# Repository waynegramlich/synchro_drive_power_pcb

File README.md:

# synchro_drive_power_pcb

This boad can provide power distribution for up to 4
Synchro Drive Motor PCB's.

## Revision A

Connectors N9, N10, N11, and N12 are 26 pin ribbon cable connectors
that provide:

* Motor power

* Logic power

* CAN bus daisy chain

* 2 Selection lines (Front/Back, Left/Right)

Connector N1 is used to provide 7.2V (i.e. RC battery pack
voltage) for logic power.  Connector N2 is conneceted to a DPDT
switch to turn logic power on and off.

Connectors N3 through N7 provicde a chain of connectors for:

* 2 12 Volt batters for a total of 24 Volts

* A DPDT connection to turn motor power on and off

* 2 emergency stop connection that will disable motor power only.

Connectors N8 and N13 are MakerBus connectors that can be
connected to other MakerBus modules.

Jumper J1 can be used to terminate the CAN bus at N13.

There are 6 test points:

* 2 for logic power/ground.

* 2 for motor power/ground.

* 2 for an extra termination resistor.

There are 4 5mm mounting holes that are on an 80mm by 80mm square.

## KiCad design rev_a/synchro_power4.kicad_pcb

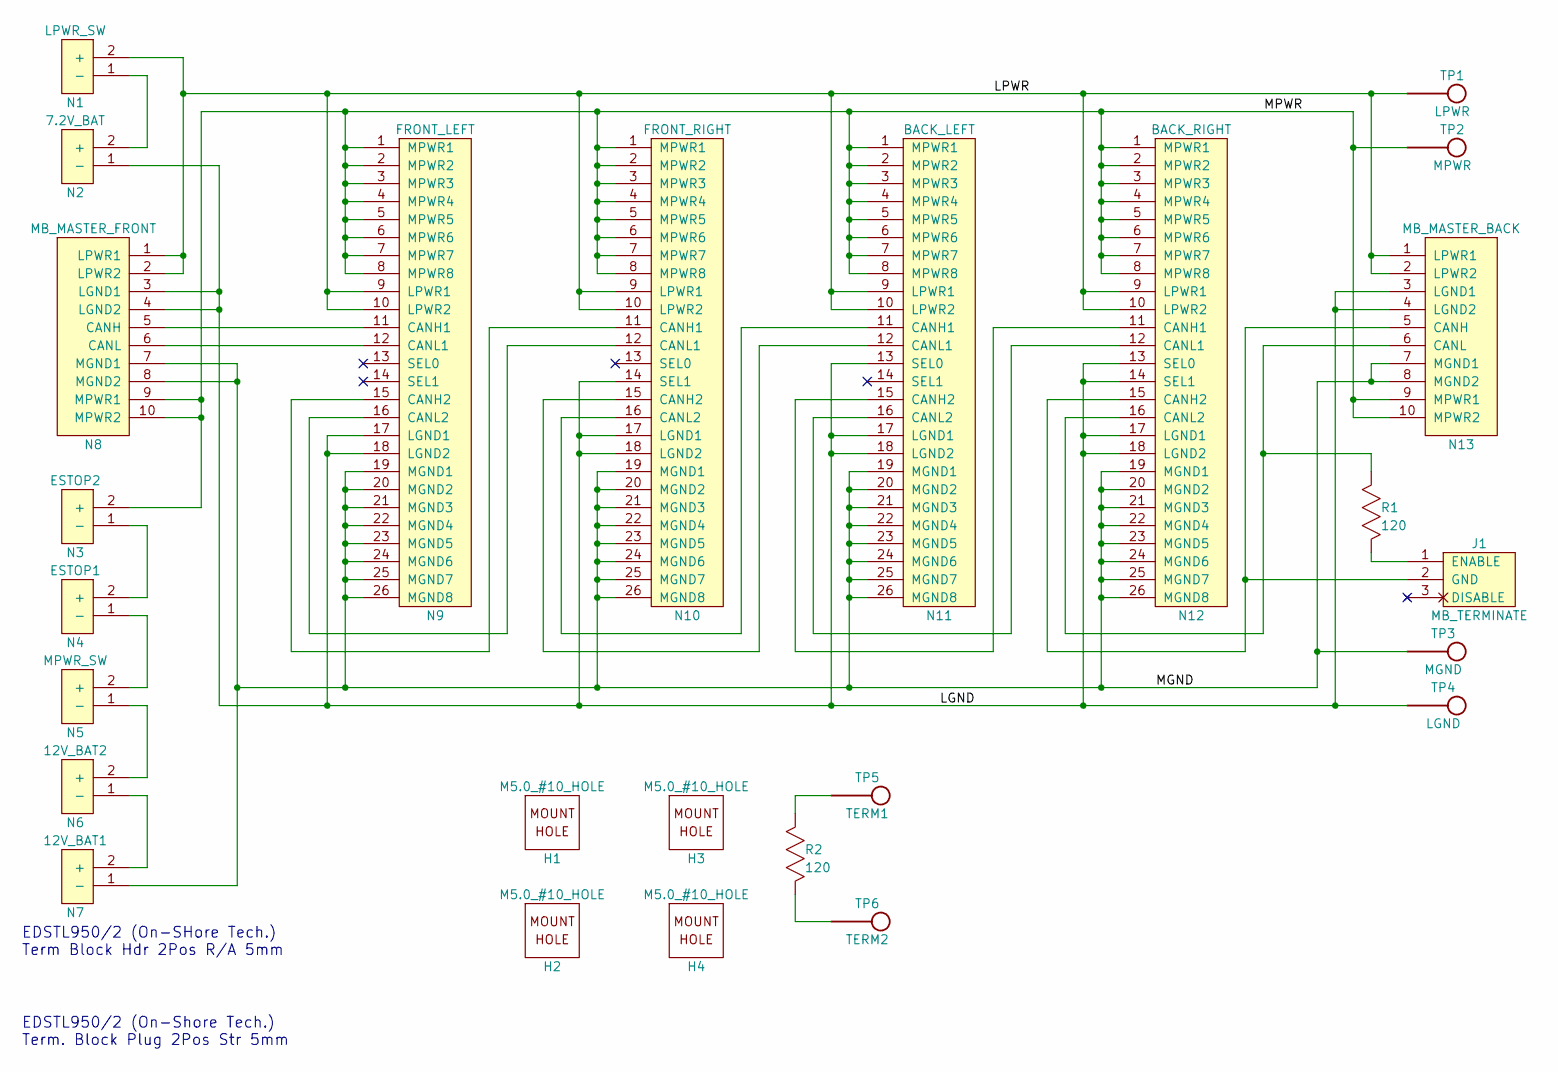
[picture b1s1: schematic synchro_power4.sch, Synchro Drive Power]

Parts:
H1, H2, H3, H4: M5.0_#10_HOLE
J1: MB_TERMINATE
N1: LPWR_SW
N2: 7.2V_BAT
N3: ESTOP2
N4: ESTOP1
N5: MPWR_SW
N6: 12V_BAT2
N7: 12V_BAT1
N8: MB_MASTER_FRONT
N9: FRONT_LEFT
N10: FRONT_RIGHT
N11: BACK_LEFT
N12: BACK_RIGHT
N13: MB_MASTER_BACK
R1, R2: 120
TP1: LPWR
TP2: MPWR
TP3: MGND
TP4: LGND
TP5: TERM1
TP6: TERM2

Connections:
/LGND: N2.1 (-), N8.3 (LGND1), N8.4 (LGND2), N9.17 (LGND1), N9.18 (LGND2), N10.14 (SEL1), N10.17 (LGND1), N10.18 (LGND2), N11.13 (SEL0), N11.17 (LGND1), N11.18 (LGND2), N12.13 (SEL0), N12.14 (SEL1), N12.17 (LGND1), N12.18 (LGND2), N13.3 (LGND1), N13.4 (LGND2), TP4.1
/LPWR: N1.2 (+), N8.1 (LPWR1), N8.2 (LPWR2), N9.9 (LPWR1), N9.10 (LPWR2), N10.9 (LPWR1), N10.10 (LPWR2), N11.9 (LPWR1), N11.10 (LPWR2), N12.9 (LPWR1), N12.10 (LPWR2), N13.1 (LPWR1), N13.2 (LPWR2), TP1.1
/MGND: N7.1 (-), N8.7 (MGND1), N8.8 (MGND2), N9.19 (MGND1), N9.20 (MGND2), N9.21 (MGND3), N9.22 (MGND4), N9.23 (MGND5), N9.24 (MGND6), N9.25 (MGND7), N9.26 (MGND8), N10.19 (MGND1), N10.20 (MGND2), N10.21 (MGND3), N10.22 (MGND4), N10.23 (MGND5), N10.24 (MGND6), N10.25 (MGND7), N10.26 (MGND8), N11.19 (MGND1), N11.20 (MGND2), N11.21 (MGND3), N11.22 (MGND4), N11.23 (MGND5), N11.24 (MGND6), N11.25 (MGND7), N11.26 (MGND8), N12.19 (MGND1), N12.20 (MGND2), N12.21 (MGND3), N12.22 (MGND4), N12.23 (MGND5), N12.24 (MGND6), N12.25 (MGND7), N12.26 (MGND8), N13.7 (MGND1), N13.8 (MGND2), TP3.1
/MPWR: N3.2 (+), N8.9 (MPWR1), N8.10 (MPWR2), N9.1 (MPWR1), N9.2 (MPWR2), N9.3 (MPWR3), N9.4 (MPWR4), N9.5 (MPWR5), N9.6 (MPWR6), N9.7 (MPWR7), N9.8 (MPWR8), N10.1 (MPWR1), N10.2 (MPWR2), N10.3 (MPWR3), N10.4 (MPWR4), N10.5 (MPWR5), N10.6 (MPWR6), N10.7 (MPWR7), N10.8 (MPWR8), N11.1 (MPWR1), N11.2 (MPWR2), N11.3 (MPWR3), N11.4 (MPWR4), N11.5 (MPWR5), N11.6 (MPWR6), N11.7 (MPWR7), N11.8 (MPWR8), N12.1 (MPWR1), N12.2 (MPWR2), N12.3 (MPWR3), N12.4 (MPWR4), N12.5 (MPWR5), N12.6 (MPWR6), N12.7 (MPWR7), N12.8 (MPWR8), N13.9 (MPWR1), N13.10 (MPWR2), TP2.1
unnamed: J1.1 (ENABLE), R1.1
unnamed: J1.2 (GND), N12.15 (CANH2), N13.5 (CANH)
unnamed: N1.1 (-), N2.2 (+)
unnamed: N3.1 (-), N4.2 (+)
unnamed: N4.1 (-), N5.2 (+)
unnamed: N5.1 (-), N6.2 (+)
unnamed: N6.1 (-), N7.2 (+)
unnamed: N8.5 (CANH), N9.11 (CANH1)
unnamed: N8.6 (CANL), N9.12 (CANL1)
unnamed: N9.15 (CANH2), N10.11 (CANH1)
unnamed: N9.16 (CANL2), N10.12 (CANL1)
unnamed: N10.15 (CANH2), N11.12 (CANL1)
unnamed: N10.16 (CANL2), N11.11 (CANH1)
unnamed: N11.15 (CANH2), N12.11 (CANH1)
unnamed: N11.16 (CANL2), N12.12 (CANL1)
unnamed: N12.16 (CANL2), N13.6 (CANL), R1.2
unnamed: R2.1, TP6.1
unnamed: R2.2, TP5.1

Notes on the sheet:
EDSTL950/2 (On-SHore Tech.) Term Block Hdr 2Pos R/A 5mm
EDSTL950/2 (On-Shore Tech.) Term. Block Plug 2Pos Str 5mm

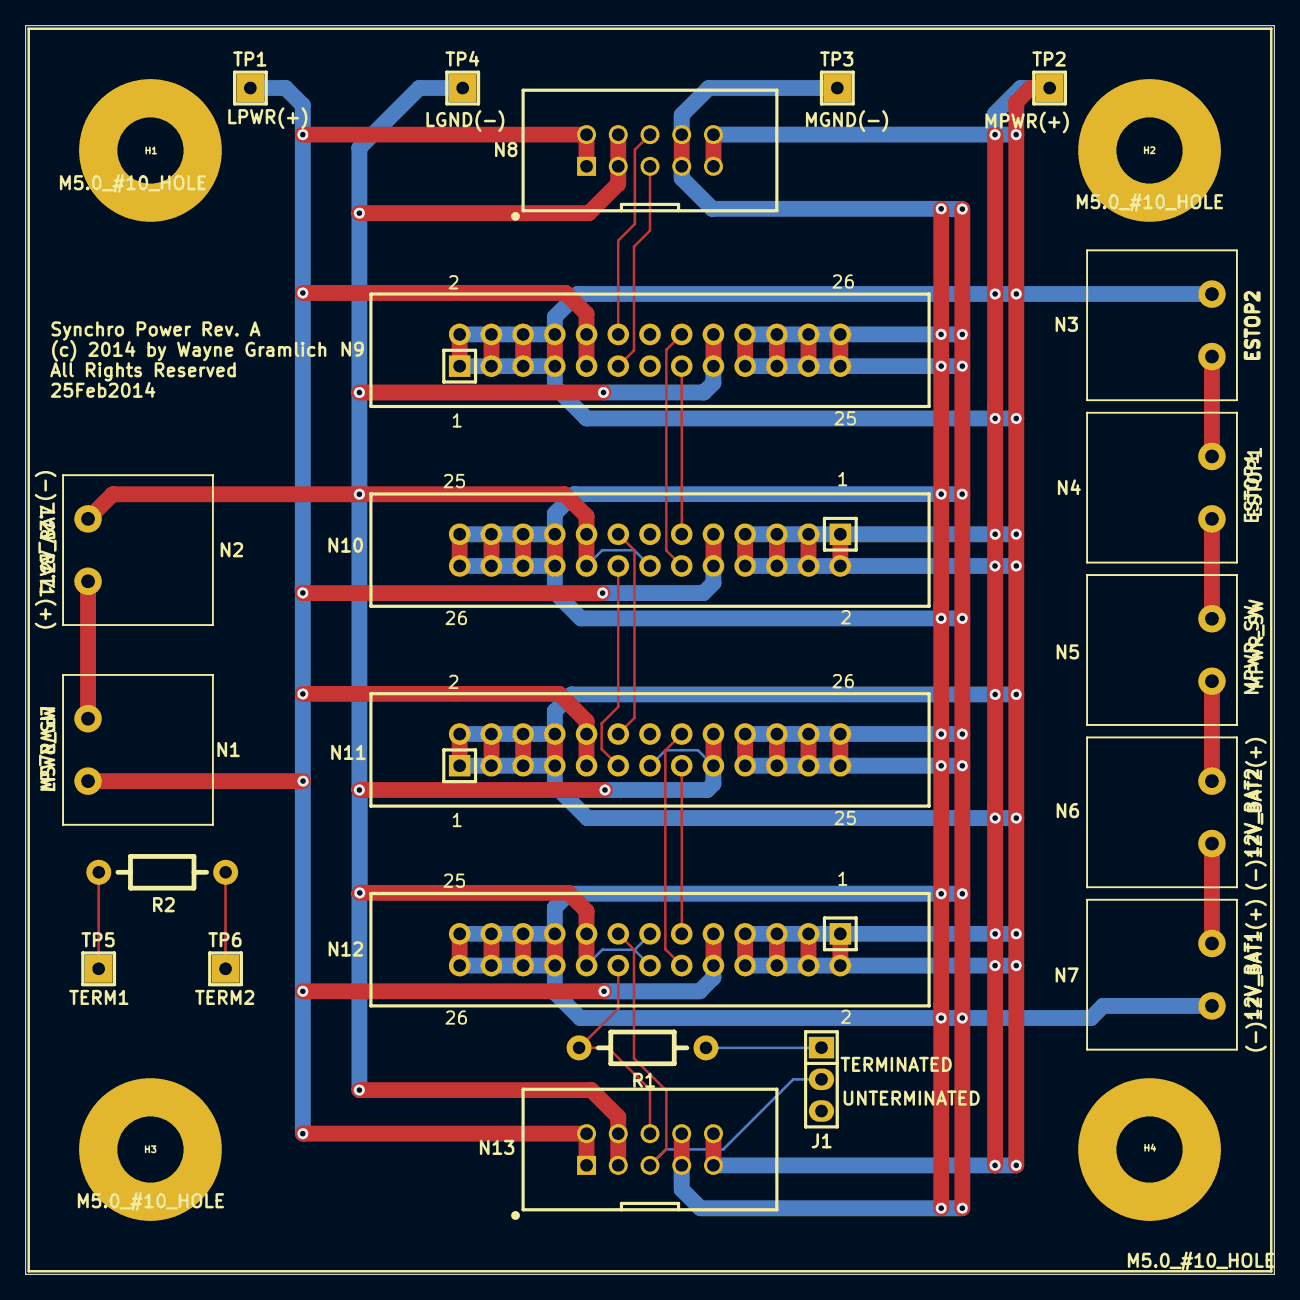
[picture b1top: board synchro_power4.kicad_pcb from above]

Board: 2 copper layers, 100.0 x 100.0 mm, 26 parts (0 on the bottom side), 22 nets.

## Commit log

2014-02-26 Rev. A is nearly ready.
2014-02-26 Rev. A is ready.

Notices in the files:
rev_a/synchro_power4.kicad_pcb:
(c) 2014 by Wayne Gramlich
All Rights Reserved
